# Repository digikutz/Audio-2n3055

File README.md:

Audio-2n3055
============

The Audio-2n3055 project aims to use common power transistors to make a high-fidelity high-power audio amp

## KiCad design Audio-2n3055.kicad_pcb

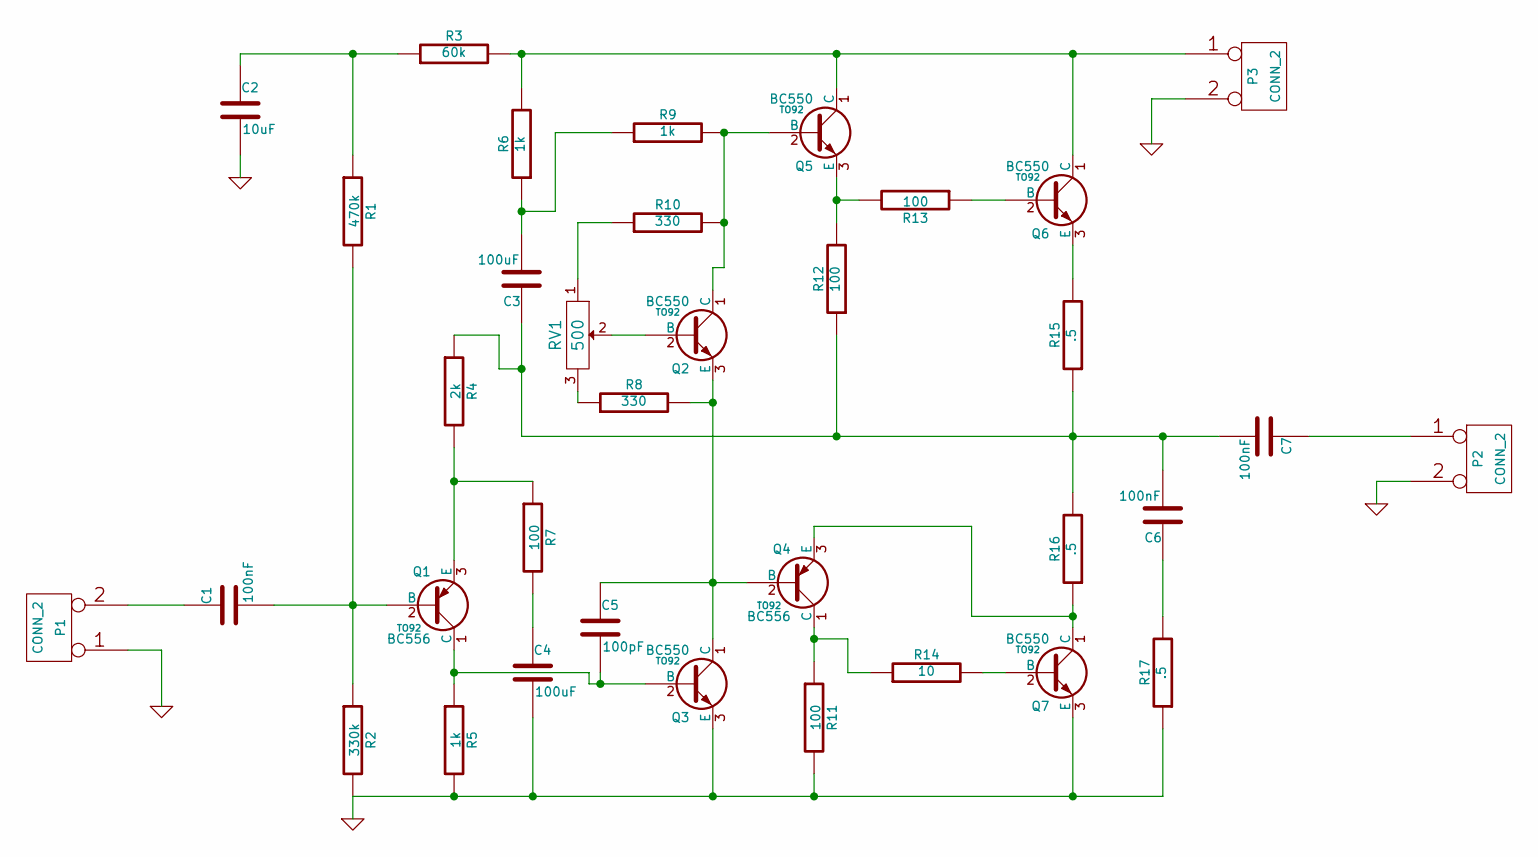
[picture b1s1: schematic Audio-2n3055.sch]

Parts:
C1, C6, C7: 100nF
C2: 10uF
C3, C4: 100uF
C5: 100pF
P1, P2, P3: CONN_2
Q1, Q4: BC556; TO92
Q2, Q3, Q5, Q6, Q7: BC550; TO92
R1: 470k
R2: 330k
R3: 60k
R4: 2k
R5, R6, R9: 1k
R7, R11, R12, R13: 100
R8, R10: 330
R14: 10
R15, R16, R17: .5
RV1: 500

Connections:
GND: C2.2, C4.2, P1.1, P2.2 (PM), P3.2 (PM), Q3.3 (E), Q7.3 (E), R2.2, R5.2, R11.2, R17.1
unnamed: Q4.1 (C), R11.1, R14.1
unnamed: Q7.2 (B), R14.2
unnamed: Q4.3 (E), Q7.1 (C), R16.1
unnamed: Q5.3 (E), R12.2, R13.2
unnamed: Q2.2 (B), RV1.2
unnamed: R8.1, RV1.3
unnamed: Q6.2 (B), R13.1
unnamed: C3.2, R6.1, R9.1
unnamed: R10.1, RV1.1
unnamed: C7.1, P2.1
unnamed: C1.1, P1.2 (PM)
unnamed: Q6.3 (E), R15.2
unnamed: C3.1, C6.2, C7.2, R4.1, R12.1, R15.1, R16.2
unnamed: C6.1, R17.2
unnamed: C5.2, Q1.1 (C), Q3.2 (B), R5.1
unnamed: C4.1, R7.2
unnamed: Q1.3 (E), R4.2, R7.1
unnamed: P3.1, Q5.1 (C), Q6.1 (C), R3.2, R6.2
unnamed: Q2.1 (C), Q5.2 (B), R9.2, R10.2
unnamed: C2.1, R1.1, R3.1
unnamed: C5.1, Q2.3 (E), Q3.1 (C), Q4.2 (B), R8.2
unnamed: C1.2, Q1.2 (B), R1.2, R2.1

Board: 2 copper layers, 35 parts (0 on the bottom side), 23 nets, no tracks yet.

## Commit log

2014-04-11 PCB's in progress
